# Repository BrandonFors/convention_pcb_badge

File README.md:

# Convention Badge Project

## The Idea

To create a custom and interactive badge for conventions. The badge would have at least a display and a lipo power supply and some cool designs on the pcb. It would also probably have buttons for interactivity and other fun things.

## Design

ESP32C3 microcontroller. PCB designed in KiCad. Programming done with espressif

### V1

This design features a basic form factor supporting the XIAO esp32c3 devboard along with a 2.9 inch display module. The design was never actually manufactured.

### V2

The V2 board was designed to serve as both a badge and a dev board. It hosts the esp32c3, has support for USB power and flashing, has a battery managment circuit, and various peripherals. The display circuitry still lies on a breakout board which is attached through header pins. It is designed to resemble a satelite.

This design experience was particularly new/challenging because it was the first PCB design I made where I had to consider how parts and integrated circuits interact rather than wiring pin headers together. I also had to consider manufacturing requirements, part availability, and cost.

After manufacturing this board through JLCPCB, I was able to flash the ESP32C3 over USBC and get my display, buttons, and leds working. However, there were a few mistakes within the battery managment circuit that made LiPo power unusable for this version. I was able to fix one to get battery charging working, but a misconfigured mosfet connection made powering the uC with the battery impossible without some reworking which I don't have the tools for. 

Code at this stage is pretty scrappy as the main focus was on PCB design and just getting a prototype working.

Overall, I consider this version great progress and a great step towards improving my PCB design skills. Even though the main complexity of the battery managment circuitry doesn't work, I know what to fix in my next revision. This was my first project where programming wasn't really the main focus and I feel that I have a solid understanding of what to expect the design process to look like in my next KiCad project.

### V3 

Not Started.

This version will ideally look more like a sattelite or whatever form factor represents my interests. It also may switch to a digital display to enable more interactivity than an e-ink offers. 

Things that I had to rework/need to be fixed from V2:
- N-Mosfet for power source switching must align with datasheet
- Bulk capacitor added to display's power and GND. 
- S1 on FS8205A must be connected to ground. 
- Make lanyard hole a little smaller.
- Research general rules on where to put bulk/decoupling capacitors in a design and what type of capacitors are needed in various scenarios. 

## KiCad

All relevant kicad files can be found in `convention_badge_kicad`. We'll probably start by designing a basic board that would just serve as a platform for the esp32-c3 xiao and an e-paper breakoutboard with pin headers. After that, we can scale up complexity and embed the uC on the pcb badge and choose whether or not to design the badge with an FCC connection. 

One reference we are using is Notre Dame's build-a-board workshop pcb design which features a working esp32-c3 breakout board design.

Build-A-Board Credits: https://engineering.nd.edu/news/electrical-engineering-students-create-circuit-boards-in-inaugural-build-a-board-workshop/

# Design Notes

Everything below here is scattered notes from my dev process.

## Display options

### ESP32C3
Datasheet (contains schematics): https://documentation.espressif.com/esp32-c3-wroom-02_datasheet_en.pdf

- could go with xiao module as a backup
- could break out all available gpios to exposed vias to double as a breakout board for future use

### 2.13 inch e-Paper Display Module

 https://www.buydisplay.com/black-2-13-inch-e-paper-122x250-display-module-for-arduino-raspberry-pi

Datasheet: https://www.buydisplay.com/download/manual/ER-EPD0213-2-5076_Datasheet.pdf

UC8251 Controller: https://www.buydisplay.com/download/ic/UC8251.pdf

- is a breakout board and would be good for development on a breadboard. 
- has mounting holes that would be easy to use for the badge
- tutorial exists online for developing an entire display driver for this specific board.

The raw pannel: https://www.buydisplay.com/graphic-2-13-inch-122x250-electronic-paper-display-manufacturers

### 2.9 inch e-Paper Display Module

* probably the best considering size and scalability

https://www.buydisplay.com/black-2-9-inch-e-paper-display-module-for-arduino-raspberry-pi#

Datasheet: https://www.buydisplay.com/download/manual/ER-EPD029-2-5073_Datasheet.pdf

SSD1680 Controller: https://www.buydisplay.com/download/ic/SSD1680.pdf

- development board that is slightly larger and probably better for display purposes
- option for a breakout board and raw board if we decide to integrate pannel regulation into badge

The raw pannel: https://www.buydisplay.com/serial-2-9-inch-e-paper-screen-128x296-for-electronic-shelf-label-lcd

### 2.6 inch e-Paper Display Pannel

https://www.buydisplay.com/2-6-inch-e-ink-152x296-e-paper-display-panel-red-white-black-spi

Datasheet: https://www.buydisplay.com/download/manual/ER-EPD026A1-1_Datasheet.pdf

SSD1675A Controller: https://www.buydisplay.com/download/ic/SSD1675A.pdf

FCC Cable: https://www.buydisplay.com/download/connector/ER-CON24HT-1.pdf

- doesn't have breakout board 
- slightly larger
- requires 24 pin fcc ribbon cable and a connector

## Manufacturing

Most likely JLCPCB

Will likely have to pay for at least partial assembly. 

## Price Estimate

Claude session resulted in price estimate of ~$32 per board including assembly and shipping on an order of 5.

To minimize price, we can design a one sided board (the back) and hand solder buttons and attach the scren on the front. I don't think that prevents solder mask designs on the front. 

## Design Notes

### PCB_BadgeV1

This board will utilize the XIAO ESP32 C3 and an 2.9 inch e-Paper Display Module for functionality. Both will be soldered to the badge using header pins. A 3.7V lipo battery will be soldered to the underside of the xiao module as I don't have a way to solder the pads directly to the badge board. The board will also have some buttons on remaining usable gpio pins. 

This board is largely complete and contains support for a 2.9 inch epaper breakout and and esp32 c3 xiao soldered to the board using male header pins. One pin is wired to a voltage divider for battery power readings. The board also has support for 3 standard 6mm buttons which use internal pull up resistors on the esp32-c3. Footprints are mostly for through hole breadboard components purely because I am not space constrained and wanted to design the board for components that I already had on hand to avoid shipping/assembly costs.

The odds are that this board is never manufactured just because the next one will feature more peripherals as it won't be constrained by the pinout of the xiao. V2 will support the esp32-c3 directly on the pcb, based largely on the Build-A-Board pcb mentioned above.

Note: This board does not have decoupling capacitors between the e paper display and the 3.3V xiao supply.

#### Notable Resources

XIAO Getting Started: https://wiki.seeedstudio.com/XIAO_ESP32C3_Getting_Started/

Display Datasheet: Datasheet: https://www.buydisplay.com/download/manual/ER-EPD029-2-5073_Datasheet.pdf

### PCB_BadgeV2

This board will be 4 layers with support for the esp32-c3 directly on the pcb. Whether or not the board supports the e-paper display directly with no breakout is TBD. I might opt for a hybrid board that supports both the breakout board and the raw screen with solder bridges to enable/disable either set of connections. 

Section 13 of the SSD1680 Datasheet has a diagram of exactly what the 24 pin connector should be wired to.

10k PU with a 1uF capacitor on the EN line creates a RC time constant of 10ms, allowing EN to stay low on to 3.3V stabalizes so the chip boots properly.

I need some way to handle the battery managment of this design. I think I might need a battery charging IC.

Need to make sure that parts are in stock in jlcpcb

https://jlcpcb.com/parts

Going to create a charging/bms circuit using:
- TP4056
- DW10A
- FS8205A

Then I can use TLV75733P for voltage regulation and hook everything to the output 3.3V from there.

Added breakout pins for debugging purposes

Main section is 54 tall and 90 wide -> top and bottom pannels can be 19 tall w/ 3mm gaps between board and pannels

Hex design is 17.5mm tall and 88.1 mm wide

### Code Development

Notable E-Paper Sections:
- 9: Operation Flow 
- 8: Command Description
- 12.1: Timing table and diagram

Using EastRising's example code and the SD1680 documentation, I've got a working program that prints out an example image onto the screen. The display is electronically configured to be used vertically, but horizontal use is easily fixed with some clever frame buffer software. I'm just going to make it cycle through preconfigured bitmaps with the buttons to control the cycle.

Bitmap Img Converter: https://javl.github.io/image2cpp/

LUT Experiment Notes:
Refresh by default is pretty slow at 1.5 sec
- May be able to cut down with custom lut -> tradeoff is quality bc OTP lut does a full cycle on all pixels to fully clear them
Custom lut provided by east rising results in 0.9 sec refresh but leaves a faded img of the previous frame

In the future I can diff two frame buffers to find the changed pixels/sections and then use the xram and yram start/end points to selectively update the screen to avoid some of the anoying refresh.

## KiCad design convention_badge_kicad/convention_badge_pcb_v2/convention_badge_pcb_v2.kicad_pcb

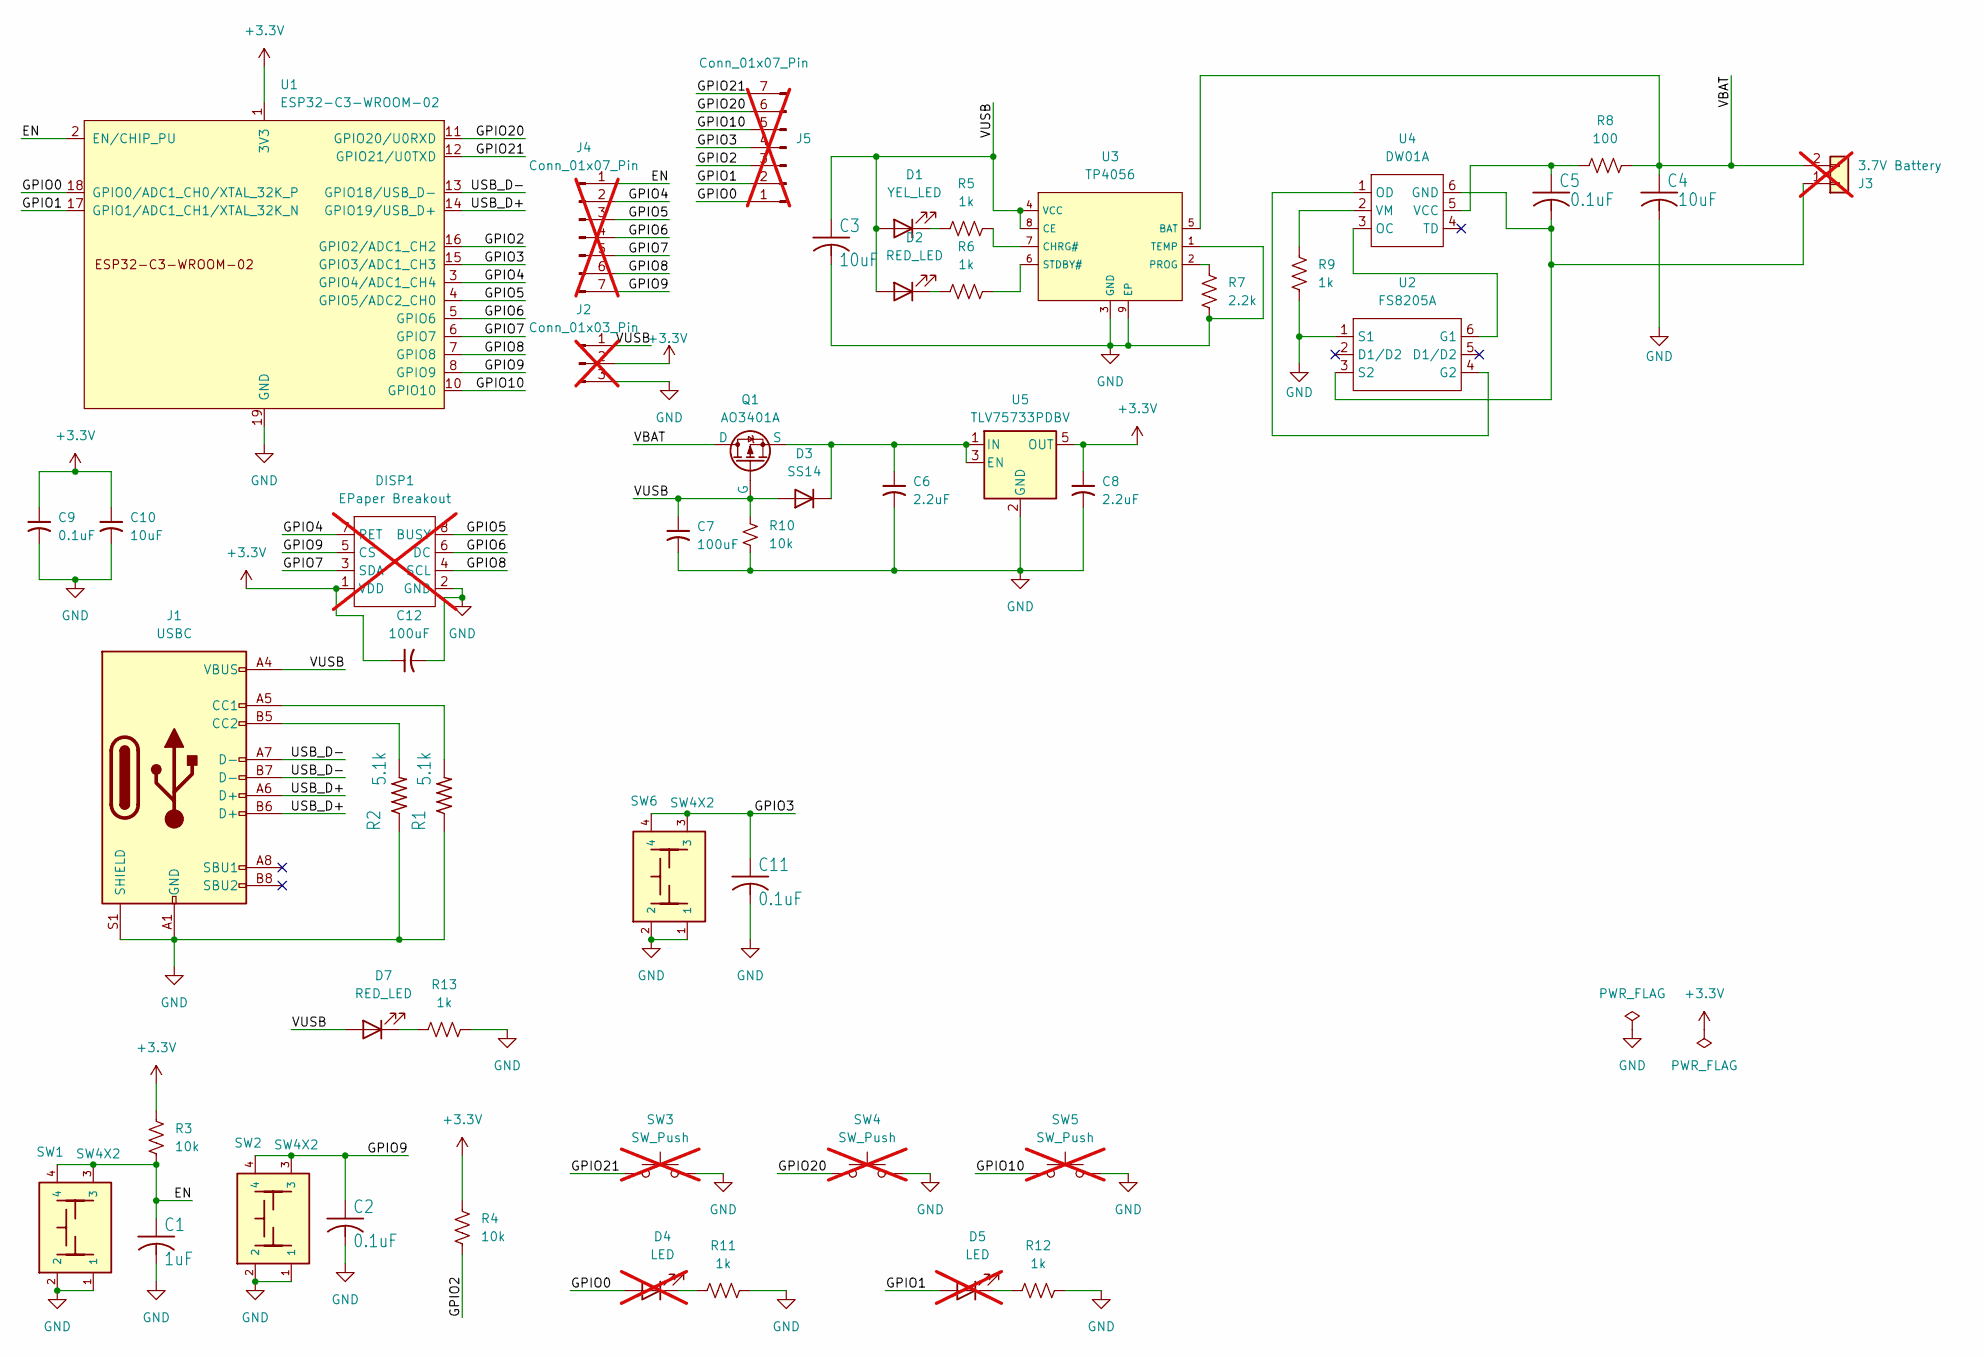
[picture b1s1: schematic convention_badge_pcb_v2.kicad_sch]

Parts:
C1: 1uF; C_0603_1608Metric; LCSC C15849
C2, C5, C9, C11: 0.1uF; C_0603_1608Metric; LCSC C14663
C3, C4, C10: 10uF; C_CASE-A-3216-18(mm); LCSC C7171
C6, C8: 2.2uF; C_0603_1608Metric; LCSC C23630
C7, C12: 100uF; C_CASE-B-3528-21(mm); LCSC C122271
D1: YEL_LED; D_0603; LCSC C2290
D2, D7: RED_LED; D_0603; LCSC C2286
D3: SS14; D_DO-214AC(SMA); LCSC C2480
D4, D5: LED; LED_D5.0mm; not fitted
DISP1: EPaper Breakout; 2.9_e_paper_ER-EPD029-2-5073; not fitted
J1: USBC; USB_C_Receptacle_GCT_USB4105-xx-A_16P_TopMnt_Horizontal; LCSC C2765186
J2: Conn_01x03_Pin; PinHeader_1x03_P2.54mm_Vertical; LCSC C2337; not fitted
J3: 3.7V Battery; JST_PH_S2B-PH-K_1x02_P2.00mm_Horizontal; LCSC C173752; not fitted
J4, J5: Conn_01x07_Pin; PinHeader_1x07_P2.54mm_Vertical; not fitted
Q1: AO3401A; SOT-23; LCSC C20917
R1, R2: 5.1k; R_0603; LCSC C23186
R3, R4, R10: 10k; R_0805_2012Metric; LCSC C17414
R5, R6, R9, R11, R12, R13: 1k; R_0603; LCSC C21190
R7: 2.2k; R_0603; LCSC C4190
R8: 100; R_0603; LCSC C22775
SW1, SW2, SW6: SW4X2; SW-SMD_4P-L5.1-W5.1-P3.70-LS6.5-TL-2; LCSC C318884
SW3, SW4, SW5: SW_Push; SW_PUSH_6mm; not fitted
U1: ESP32-C3-WROOM-02; LCSC C2944070
U2: FS8205A; SOT-23-6; LCSC C908265
U3: TP4056; ESOP-8_L4.9-W3.9-P1.27-LS6.0-BL-EP; Part TP4056-42-ESOP8; LCSC C16581
U4: DW01A; SOT-23-6; LCSC C351410
U5: TLV75733PDBV; SOT-23-5; LCSC C485517

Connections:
+3.3V: C8.1, C9.1, C10.1, C12.1, DISP1.1 (VDD), J2.2, R3.1, R4.1, U1.1 (3V3), U5.5 (OUT)
/EN: C1.1, J4.1, R3.2, SW1.3, SW1.4, U1.2 (EN/CHIP_PU)
/GPIO0: D4.2 (A), J5.1, U1.18 (GPIO0/ADC1_CH0/XTAL_32K_P)
/GPIO1: D5.2 (A), J5.2, U1.17 (GPIO1/ADC1_CH1/XTAL_32K_N)
/GPIO2: J5.3, R4.2, U1.16 (GPIO2/ADC1_CH2)
/GPIO3: C11.1, J5.4, SW6.3, SW6.4, U1.15 (GPIO3/ADC1_CH3)
/GPIO4: DISP1.7 (RET), J4.2, U1.3 (GPIO4/ADC1_CH4)
/GPIO5: DISP1.8 (BUSY), J4.3, U1.4 (GPIO5/ADC2_CH0)
/GPIO6: DISP1.6 (DC), J4.4, U1.5 (GPIO6)
/GPIO7: DISP1.3 (SDA), J4.5, U1.6 (GPIO7)
/GPIO8: DISP1.4 (SCL), J4.6, U1.7 (GPIO8)
/GPIO9: C2.1, DISP1.5 (CS), J4.7, SW2.3, SW2.4, U1.8 (GPIO9)
/GPIO10: J5.5, SW5.1, U1.10 (GPIO10)
/GPIO20: J5.6, SW4.1, U1.11 (GPIO20/U0RXD)
/GPIO21: J5.7, SW3.1, U1.12 (GPIO21/U0TXD)
/USB_D+: J1.A6 (D+), J1.B6 (D+), U1.14 (GPIO19/USB_D+)
/USB_D-: J1.A7 (D-), J1.B7 (D-), U1.13 (GPIO18/USB_D-)
/VBAT: C4.1, J3.2, Q1.3 (D), R8.2, U3.5 (BAT)
/VUSB: C3.1, C7.1, D1.2 (A), D2.2 (A), D3.2 (A), D7.2 (A), J1.A4 (VBUS), J1.A9 (VBUS), J1.B4 (VBUS), J1.B9 (VBUS), J2.1, Q1.1 (G), R10.1, U3.4 (VCC), U3.8 (CE)
GND: C1.2, C2.2, C3.2, C4.2, C6.2, C7.2, C8.2, C9.2, C10.2, C11.2, C12.2, DISP1.2 (GND), J1.A1 (GND), J1.A12 (GND), J1.B1 (GND), J1.B12 (GND), J1.S1 (SHIELD), J2.3, R1.1, R2.1, R7.1, R9.1, R10.2, R11.2, R12.2, R13.2, SW1.1, SW1.2, SW2.1, SW2.2, SW3.2, SW4.2, SW5.2, SW6.1, SW6.2, U1.9 (GND), U1.19 (GND), U2.1 (S1), U3.1 (TEMP), U3.3 (GND), U3.9 (EP), U5.2 (GND)
unnamed: D1.1 (K), R5.1
unnamed: D2.1 (K), R6.1
unnamed: C6.1, D3.1 (K), Q1.2 (S), U5.1 (IN), U5.3 (EN)
unnamed: D4.1 (K), R11.1
unnamed: D5.1 (K), R12.1
unnamed: D7.1 (K), R13.1
unnamed: J1.A5 (CC1), R1.2
unnamed: J1.B5 (CC2), R2.2
unnamed: C5.2, J3.1, U2.3 (S2), U4.6 (GND)
unnamed: U2.6 (G1), U4.3 (OC)
unnamed: U2.4 (G2), U4.1 (OD)
unnamed: R5.2, U3.7 (CHRG#)
unnamed: R7.2, U3.2 (PROG)
unnamed: R6.2, U3.6 (STDBY#)
unnamed: C5.1, R8.1, U4.5 (VCC)
unnamed: R9.2, U4.2 (VM)

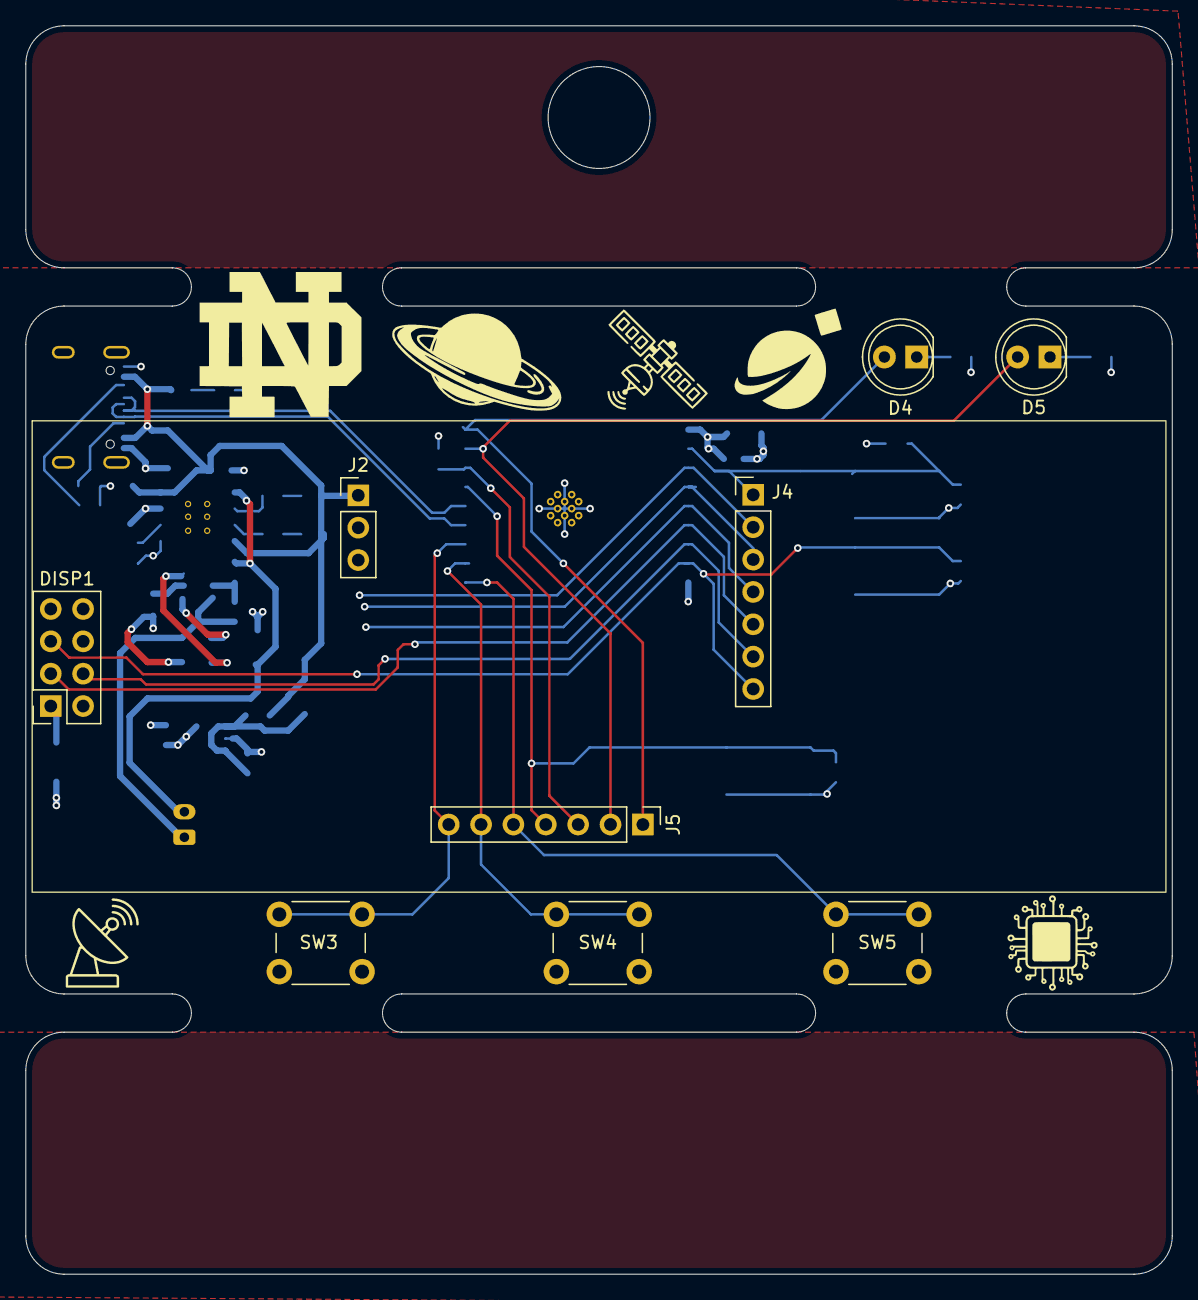
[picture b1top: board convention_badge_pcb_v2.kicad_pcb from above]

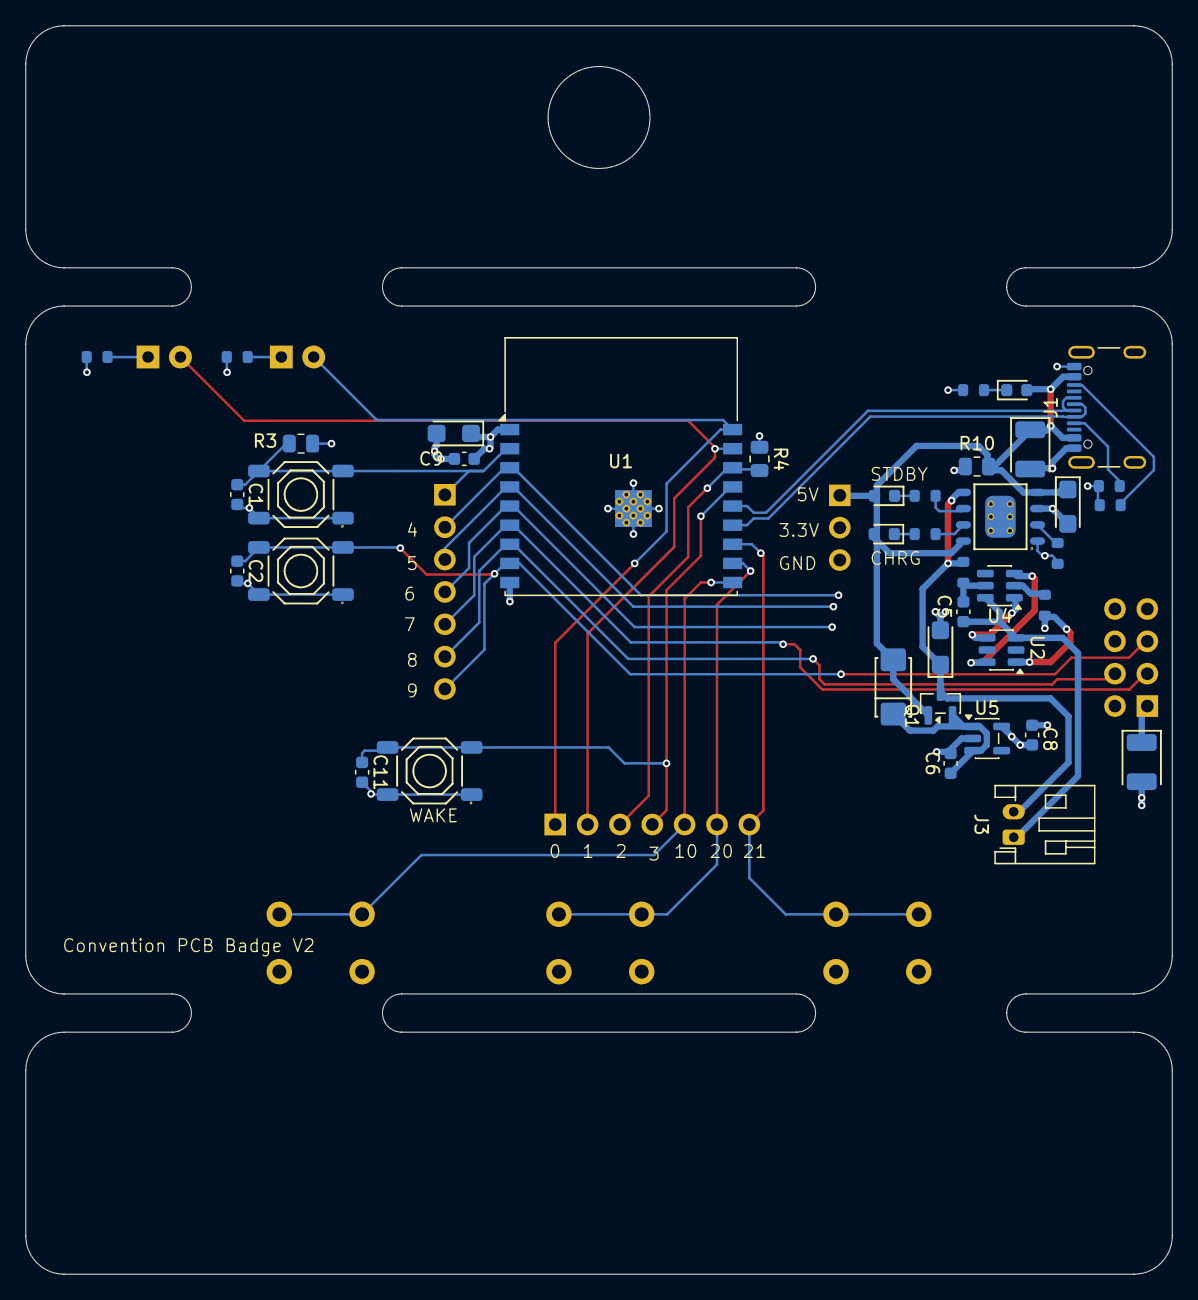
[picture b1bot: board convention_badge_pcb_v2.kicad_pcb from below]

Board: 4 copper layers, 90.0 x 98.0 mm, 49 parts (40 on the bottom side), 36 nets.

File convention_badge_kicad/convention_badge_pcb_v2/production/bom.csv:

Designator,Footprint,Quantity,Value,LCSC Part #
C1,0603,1,1uF,C15849
"C10, C3, C4",C_CASE-A-3216-18(mm),3,10uF,C7171
"C11, C2, C5, C9",0603,4,0.1uF,C14663
"C6, C8",0603,2,2.2uF,C23630
C7,C_CASE-B-3528-21(mm),1,100uF,C122271
D1,D_0603,1,YEL_LED,C2290
"D2, D7",D_0603,2,RED_LED,C2286
D3,D_DO-214AC(SMA),1,SS14,C2480
J1,USB_C_Receptacle_GCT_USB4105-xx-A_16P_TopMnt_Horizontal,1,USBC,C2765186
J3,JST_PH_S2B-PH-K_1x02_P2.00mm_Horizontal,1,3.7V Battery,C173752
Q1,SOT-23,1,AO3401A,C20917
"R1, R2",R_0603,2,5.1k,C23186
"R10, R3, R4",0805,3,10k,C17414
"R11, R12, R13, R5, R6, R9",R_0603,6,1k,C21190
R7,R_0603,1,2.2k,C4190
R8,R_0603,1,100,C22775
"SW1, SW2, SW6",SW-SMD_4P-L5.1-W5.1-P3.70-LS6.5-TL-2,3,SW4X2,C318884
U1,ESP32-C3-WROOM-02,1,ESP32-C3-WROOM-02,C2944070
U2,SOT-23-6,1,FS8205A,C908265
U3,ESOP-8_L4.9-W3.9-P1.27-LS6.0-BL-EP,1,TP4056,C16581
U4,SOT-23-6,1,DW01A,C351410
U5,SOT-23-5,1,TLV75733PDBV,C485517

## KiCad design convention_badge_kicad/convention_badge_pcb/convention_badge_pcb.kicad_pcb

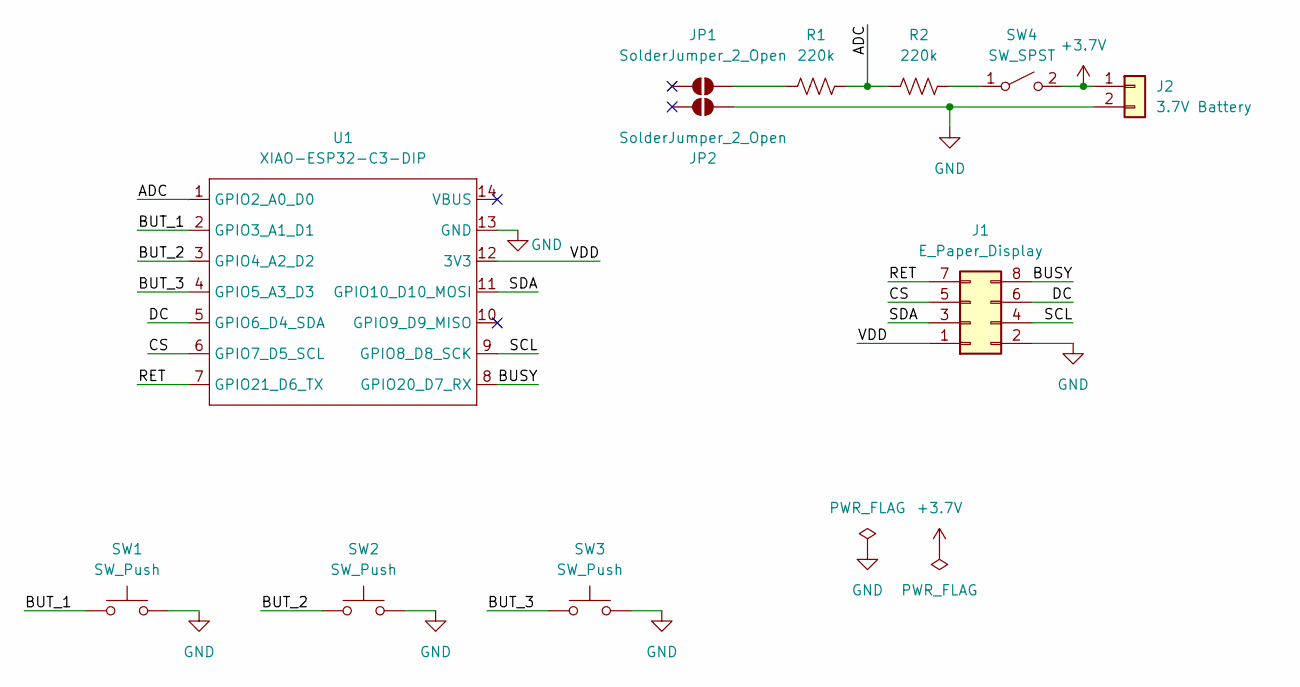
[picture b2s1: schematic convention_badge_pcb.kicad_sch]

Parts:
J1: E_Paper_Display; 2.9_e_paper_ER-EPD029-2-5073
J2: 3.7V Battery; JST_PH_S2B-PH-K_1x02_P2.00mm_Horizontal
JP1, JP2: SolderJumper_2_Open; SolderJumper-2_P1.3mm_Open_TrianglePad1.0x1.5mm
R1, R2: 220k; R_Axial_DIN0207_L6.3mm_D2.5mm_P7.62mm_Horizontal
SW1, SW2, SW3: SW_Push; SW_PUSH_6mm
SW4: SW_SPST; SW_Slide-03_Wuerth-WS-SLTV_10x2.5x6.4_P2.54mm
U1: XIAO-ESP32-C3-DIP

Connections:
+3.7V: J2.1, SW4.2 (B)
/ADC: R1.1, R2.2, U1.1 (GPIO2_A0_D0)
/BUSY: J1.8, U1.8 (GPIO20_D7_RX)
/BUT_1: SW1.1, U1.2 (GPIO3_A1_D1)
/BUT_2: SW2.1, U1.3 (GPIO4_A2_D2)
/BUT_3: SW3.1, U1.4 (GPIO5_A3_D3)
/CS: J1.5, U1.6 (GPIO7_D5_SCL)
/DC: J1.6, U1.5 (GPIO6_D4_SDA)
/RET: J1.7, U1.7 (GPIO21_D6_TX)
/SCL: J1.4, U1.9 (GPIO8_D8_SCK)
/SDA: J1.3, U1.11 (GPIO10_D10_MOSI)
/VDD: J1.1, U1.12 (3V3)
GND: J1.2, J2.2, JP2.2 (B), SW1.2, SW2.2, SW3.2, U1.13 (GND)
unnamed: JP1.2 (B), R1.2
unnamed: R2.1, SW4.1 (A)

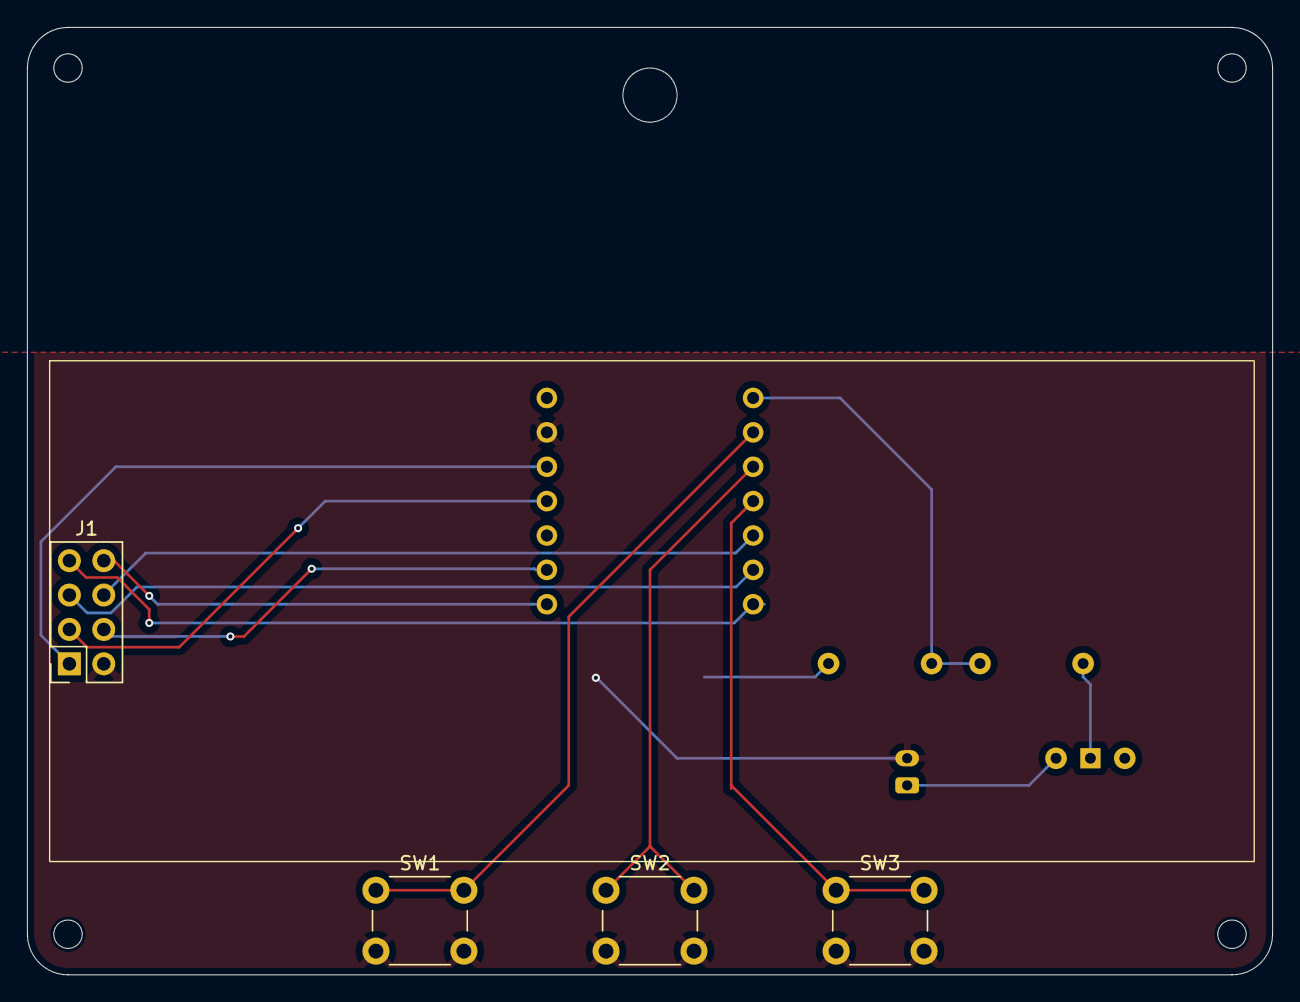
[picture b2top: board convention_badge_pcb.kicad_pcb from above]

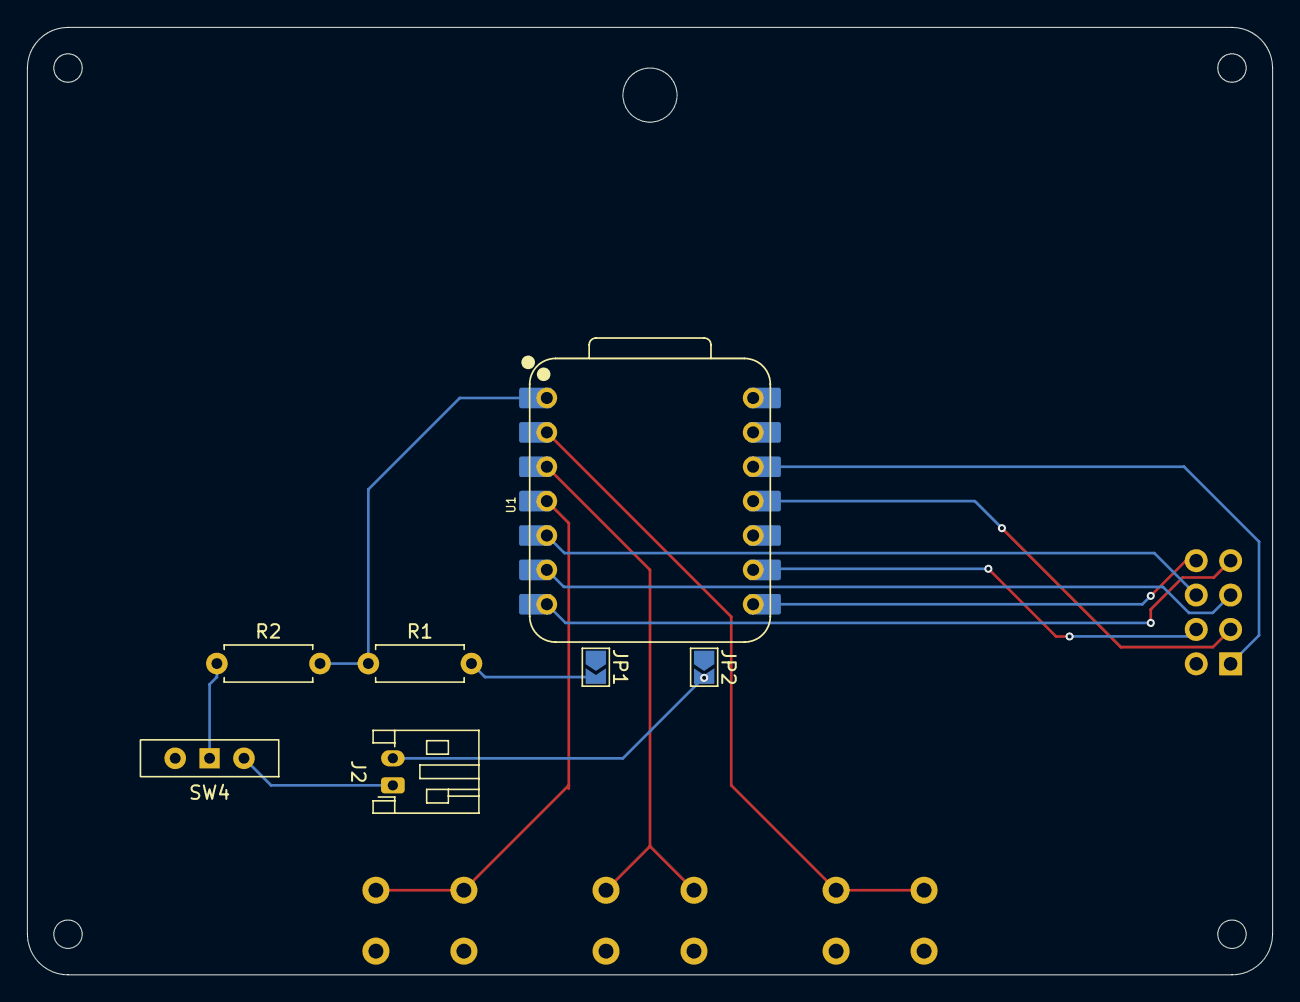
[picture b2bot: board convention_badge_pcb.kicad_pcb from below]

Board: 2 copper layers, 92.0 x 70.0 mm, 11 parts (7 on the bottom side), 15 nets.

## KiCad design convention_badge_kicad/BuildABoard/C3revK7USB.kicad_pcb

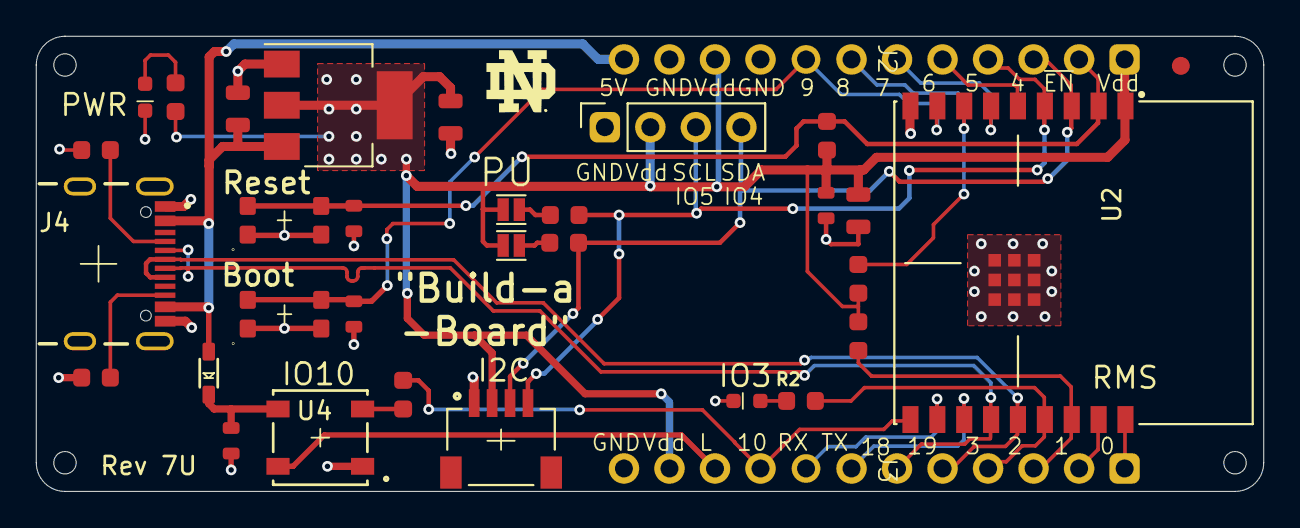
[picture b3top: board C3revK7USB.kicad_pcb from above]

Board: 2 copper layers, 68.5 x 25.4 mm, 38 parts (0 on the bottom side), 28 nets.

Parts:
C1, C5: 10uf; STA_RMCF0805_STP
C2: 22uf; STA_RMCF0805_STP
C3, C6: .1uf; C0603
C4, C7: 1uf; C0603
D1: 1N4148; SOD323
FID1: Fiducial; Fiducial_1mm_Mask2mm
H1, H2, H3, H4: MountingHole; MountingHole_Small
J1: I2C; JST04_1MM_RA
J2, J3: Conn_01x12_Pin; Pin12rms
J4: USBC; GCT4105
JP1, JP3: DNP; Jumper_NO_Small
JP2: OLED; 1x4 Socket
LED1: Green; LED_0603
LED2: Blue; LED_0603
Logo1: LOGO; blocknd5x5
R1, R2: 1k; R0603
R3, R4, R5: 10k; R0603
R6, R7: 4.7k; R0603
R14: 470; R0603
R16, R17: 5.1k; R0603
SW1, SW2: SW4X2; PB4X2
U1: AZ1117; SOT223
U2: ESP32-C3; ESP32-C3-WROOM
U4: IN-5X5-LED; LED5x5mm

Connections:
/CC1: J4.A5 (CC1), R17.2
/CC2: J4.B5 (CC2), R16.2
/D+: J3.5, J4.A6 (DP), J4.B6 (DP), U2.14 (IO19)
/D-: J3.6, J4.A7 (DN), J4.B7 (DN), U2.13 (IO18)
/IO0: J3.1, U2.18 (IO0)
/IO1: J3.2, U2.17 (IO1)
/IO2: J3.3, R3.1, U2.16 (IO2)
/IO3: J3.4, R2.2, U2.15 (IO3)
/IO4/SDA: J1.3 (SDA), J2.3, JP2.4 (SDA), R6.1, U2.3 (IO4)
/IO5/SCL: J1.4 (SCL), J2.4, JP2.3 (SCL), R7.1, U2.4 (IO5)
/IO6: J2.5, U2.5 (IO6)
/IO7: J2.6, U2.6 (IO7)
/IO8: J2.7, R4.1, U2.7 (IO8)
/IO9: C3.1, J2.8, SW2.2, SW2.3, U2.8 (IO9)
/IO10: J3.9, R14.1, U2.10 (IO10)
/LED_O: J3.10, U4.2 (DOUT)
/VUSB: C1.1, D1.2, J2.12, J4.A4_B9 (VUSB), J4.B4_A9 (VUSB), U1.3 (INPUT)
/W-RX: J3.8, U2.11 (RXD)
/W-TX: J3.7, U2.12 (TXD)
/~EN: C4.1, J2.2, R5.1, SW1.2, SW1.3, U2.2 (EN)
GND: C1.2, C2.2, C3.2, C4.2, C5.2, C6.2, C7.2, J1.1 (GND), J2.9, J2.11, J3.12, J4.A1_B12 (GND), J4.B1_A12 (GND), J4.S1 (SHELL_GND), J4.S2 (SHELL_GND), J4.S3 (SHELL_GND), J4.S4 (SHELL_GND), JP2.1 (GND), LED1.1 (C), LED2.1 (C), R16.1, R17.1, SW1.1, SW1.4, SW2.1, SW2.4, U1.1 (GND), U2.9 (GND), U2.19 (GND), U2.20 (GND), U2.21 (GND), U2.22 (GND), U2.23 (GND), U2.24 (GND), U2.25 (GND), U2.26 (GND), U2.27 (GND), U4.1 (GND)
unnamed: JP1.1 (A), R6.2
unnamed: JP3.1 (A), R7.2
unnamed: LED1.2 (A), R1.1
unnamed: LED2.2 (A), R2.1
unnamed: C7.1, D1.1, U4.4 (5VDC)
unnamed: R14.2, U4.3 (DIN)
VDD: C2.1, C5.1, C6.1, J1.2 (VCC), J2.1, J2.10, J3.11, JP1.2 (B), JP2.2 (VDD), JP3.2 (B), R1.2, R3.2, R4.2, R5.2, U1.2 (OUTPUT), U2.1 (3V3)

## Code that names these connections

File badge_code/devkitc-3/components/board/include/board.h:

#ifndef BOARD_H
#define BOARD_H

#include <stdint.h>


// Button Pins
#define BUT_1_PIN 21
#define BUT_2_PIN 20
#define BUT_3_PIN 10

// E-Paper pins 
#define MOSI_PIN 7 // SPI
#define SCLK_PIN 8 // SPI
#define CS_PIN   9 // GPIO OUT
#define DC_PIN   6 // GPIO OUT
#define RET_PIN  4 // GPIO OUT // Hardware Reset
#define BUSY_PIN 5 // GPIO IN

//LEDS
#define RED_LED_PIN 0
#define YEL_LED_PIN 1



#endif

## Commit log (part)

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2026-05-25 initial commit, brief design outline
2026-05-25 modified readme format
2026-05-25 initial kicad commit
2026-05-25 updated readme and added kicad board reference
2026-05-31 updated board options, prob going with 2.9 incher
2026-06-01 v1 schematic and parts list
2026-06-04 created footprint for display and made a (very) rough layout of the board
2026-06-06 finished v1 layout, will serve as backup for if v2 is unfeasable
2026-06-07 modified the board and generated gerbers
2026-06-07 modified readme
2026-06-09 began code layout
2026-06-10 begining development of hal, and code barebones
2026-06-10 Added Notes on PCB layout
2026-06-12 built a little more hal and fixed gpio conflict
2026-06-14 working epaper display with cycling between set bitmaps
2026-06-14 Added notes for PCB iteration 2
2026-06-19 v2 pcb design progressing
2026-06-21 schematic minus e paper integration complete
2026-06-22 layout is almost complete, kind of a rats nest
2026-06-23 cleaned up layout and seperated breakout headers.
2026-06-25 made board outline
2026-06-26 updated with part numbers and modified board to account for avail parts
2026-06-27 added solar pannel design, almost ready to order
2026-06-29 submitted to jlcpcb
